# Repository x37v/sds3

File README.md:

sds3
====

SDS3 clone project - these files have not been succesfully built yet

Long thread on electro-music.com that led to fixes in the original schematic from boardmember Theff, and a working SMT run from xpmtl
http://electro-music.com/forum/topic-16985.html&postorder=asc

some troubleshooting info here: http://electro-music.com/forum/topic-16985-300.html

xpmtl's SMT design is here:
http://xpmtl.net/sdiy/projects/simmons-sds-3-voice/

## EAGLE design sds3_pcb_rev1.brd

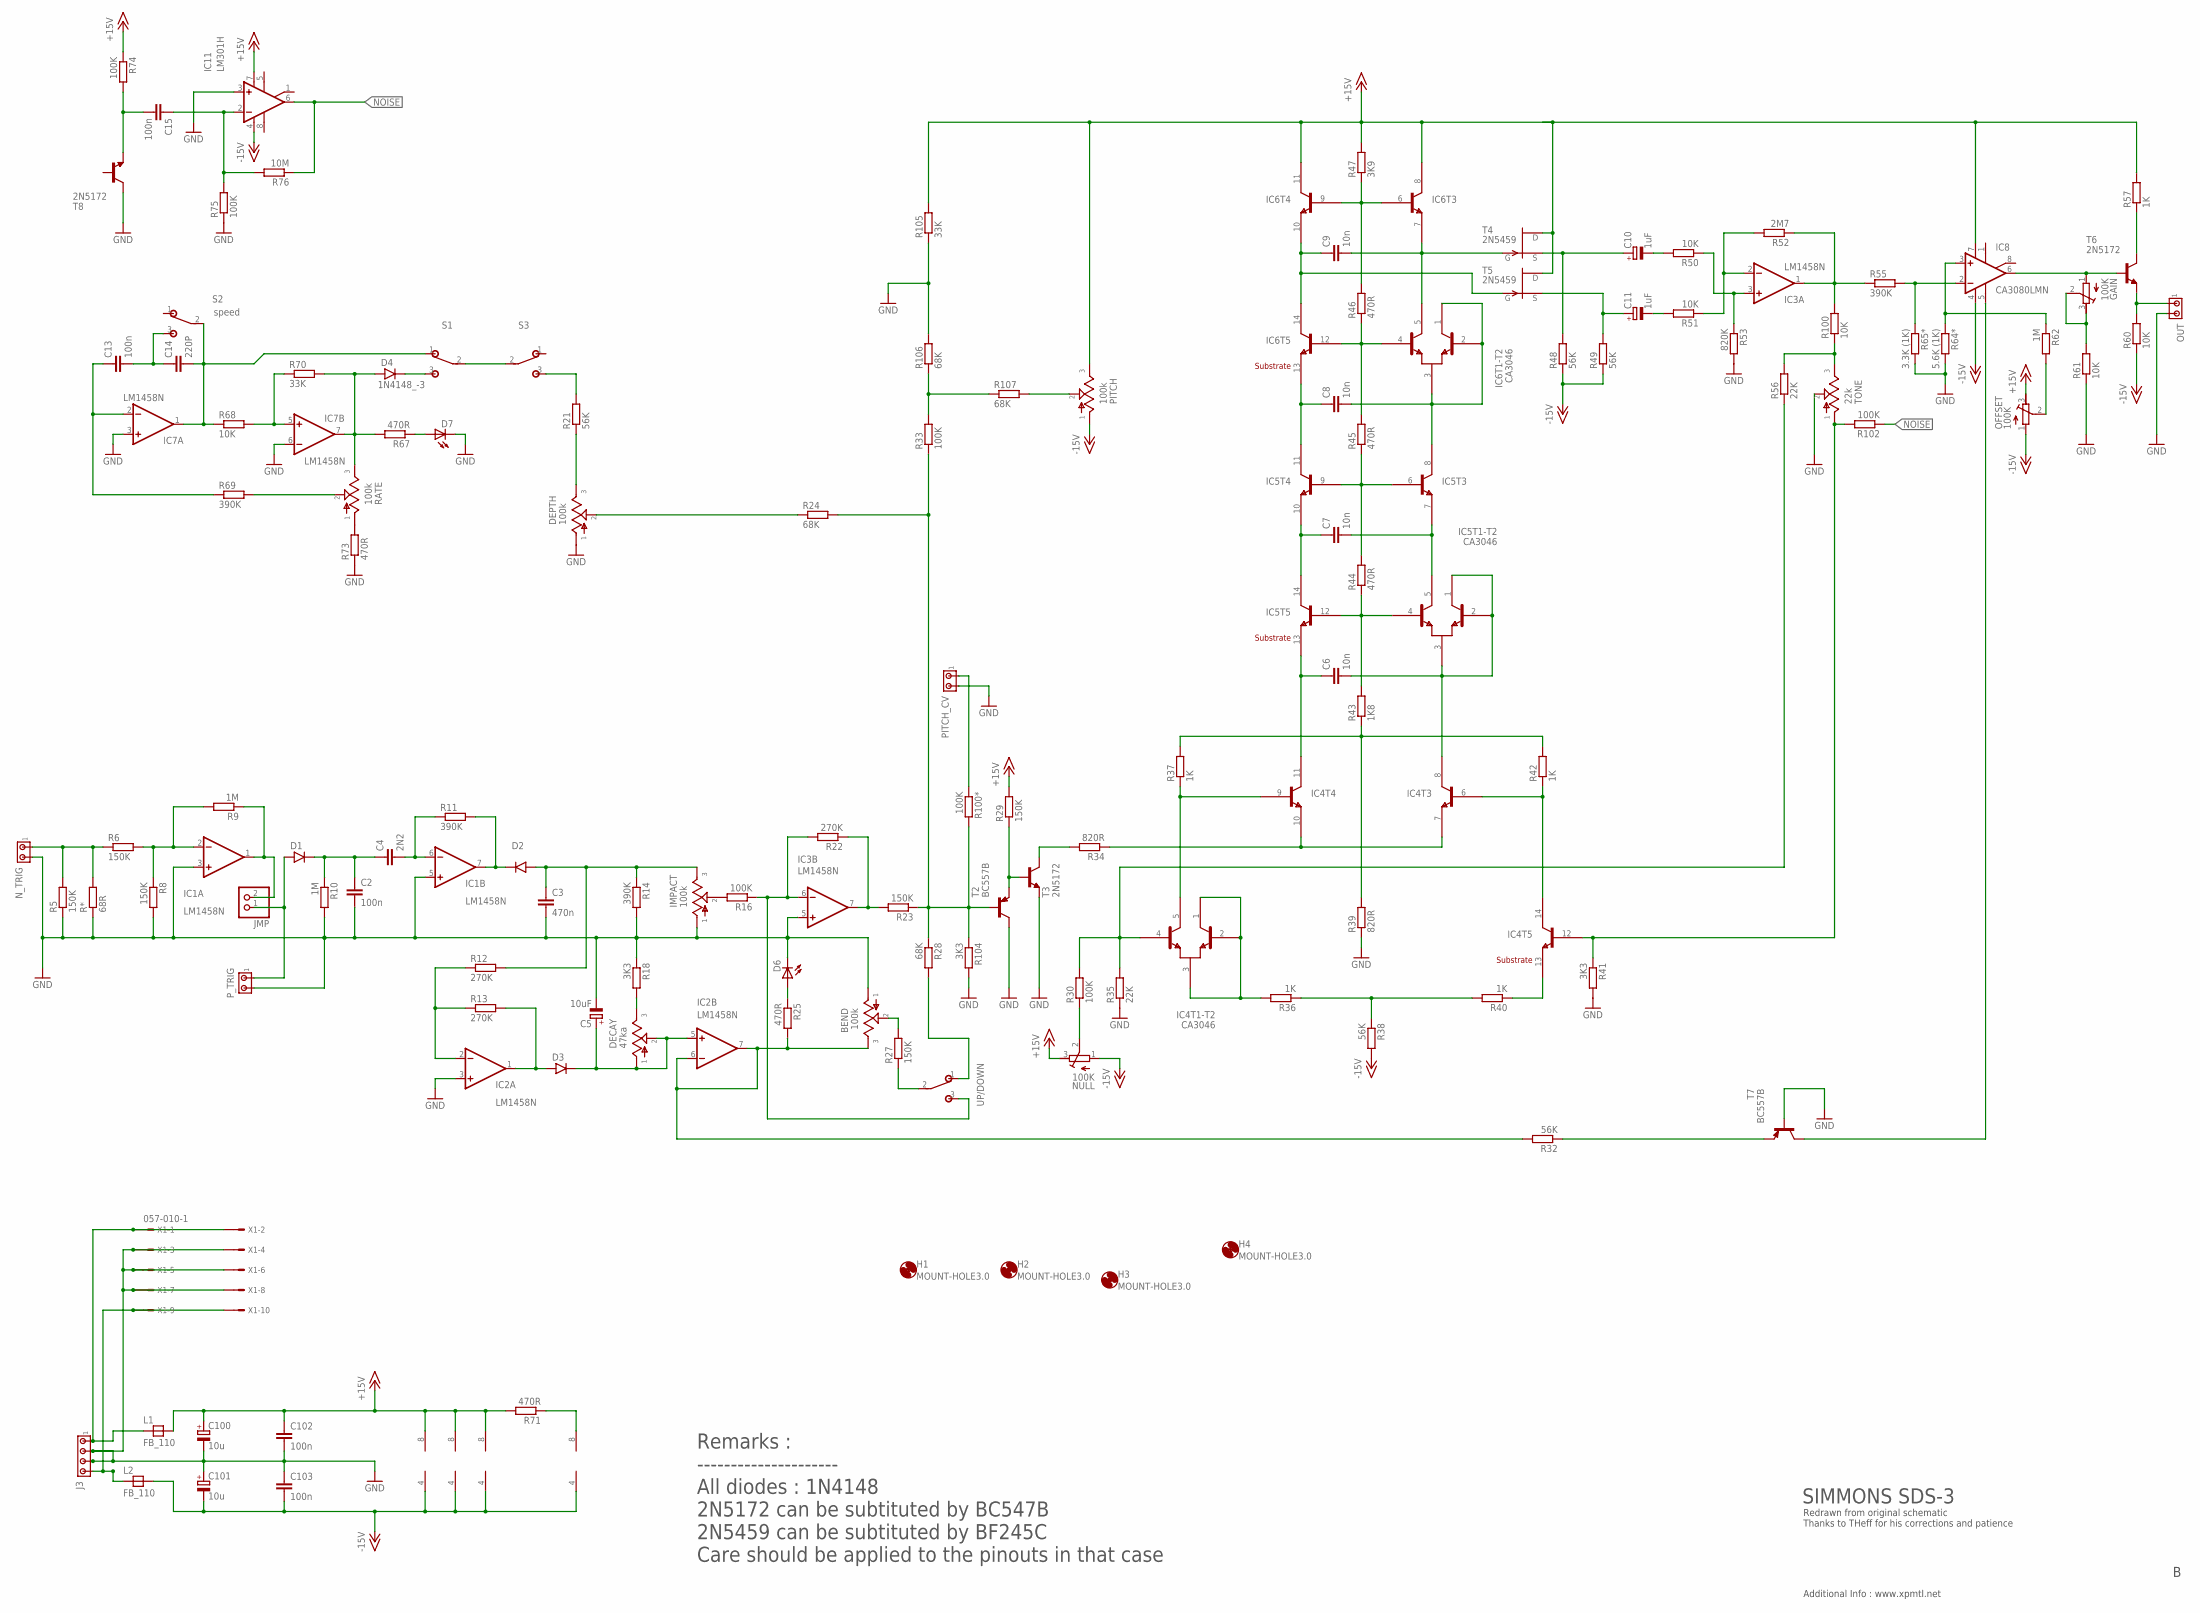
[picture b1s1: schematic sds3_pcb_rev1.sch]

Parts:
BEND: 100k; POT
C2, C13, C15, C102, C103: 100n; C050-025X075
C3: 470n; C050-025X075
C4: 2N2; C050-025X075
C5: 10uF; E2,5-6
C6, C7, C8, C9: 10n; C050-025X075
C10, C11: 1uF; E2,5-6
C14: 220P; C050-025X075
C100, C101: 10u; B45181A
D1, D2, D3, D4: 1N4148_-3; DO35-3
D6, D7: LED5MM
DECAY: 47ka; POT
DEPTH: 100k; POT
GAIN: 100K; RTRIM3296W
H1, H2, H3, H4: MOUNT-HOLE3.0; 3,0
IC1, IC2, IC3, IC7: LM1458N; DIL08
IC4, IC5, IC6: CA3046; DIL14
IC8: CA3080LMN; DIL08
IC11: LM301H; DIL08
IMPACT: 100k; POT
J3: MTA04-156; 1X4MTA
JMP: PINHD-1X2; 1X02
L1, L2: FB_110; FB-110
NULL: 100K; RTRIM3296W
N_TRIG: MTA02-100; 10X02MTA
OFFSET: 100K; RTRIM3296W
OUT: MTA02-100; 10X02MTA
PITCH: 100k; POT
PITCH_CV: MTA02-100; 10X02MTA
P_TRIG: MTA02-100; 10X02MTA
R5, R6, R8, R23, R27, R29: 150K; 0309V
R9, R10, R62: 1M; 0309V
R11, R14, R55, R69: 390K; 0309V
R12, R13, R22: 270K; 0309V
R16, R30, R33, R74, R75, R100*, R102: 100K; 0309V
R18, R41, R104: 3K3; 0309V
R21, R32, R38, R48, R49: 56K; 0309V
R24, R28, R106, R107: 68K; 0309V
R25, R44, R45, R46, R67, R71, R73: 470R; 0309V
R34, R39: 820R; 0309V
R35, R56: 22K; 0309V
R36, R37, R40, R42, R57: 1K; 0309V
R43: 1K8; 0309V
R47: 3K9; 0309V
R50, R51, R60, R61, R68, R100: 10K; 0309V
R52: 2M7; 0309V
R53: 820K; 0309V
R64*: 5.6K (1K); 0309V
R65*: 3.3K (1K); 0309V
R70, R105: 33K; 0309V
R76: 10M; 0309V
R*: 68R; 0309V
RATE: 100k; POT
S1: shape; SPDT
S2: speed; SPDT
S3: on/off; SPDT
T2, T7: BC557B; TO92-EBC
T3, T6, T8: 2N5172; TO92-LINE
T4, T5: 2N5459; TO92-FET2
TONE: 22k; POT
UP/DOWN: SPDTPADS; SPDT
X1: 057-010-1

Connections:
+15V: C100.+, C102.1, IC1.8 (V+), IC2.8 (V+), IC3.8 (V+), IC6.8 (C), IC6.11 (C), IC8.7 (V+), IC11.7 (V+), L1.2, NULL.3 (E), OFFSET.3 (E), PITCH.3, R29.2, R47.2, R57.2, R71.2, R74.1, R105.2, T4.D, T5.D
-15V: C101.-, C103.2, IC1.4 (V-), IC2.4 (V-), IC3.4 (V-), IC7.4 (V-), IC8.4 (V-), IC11.4 (V-), L2.2, NULL.1 (A), OFFSET.1 (A), PITCH.1, R38.2, R48.1, R49.1, R60.1
GND: BEND.1, C2.2, C3.2, C5.-, C100.-, C101.+, C102.2, C103.1, D6.K (C), D7.K (C), DEPTH.1, IC1.3 (+IN), IC1.5 (+IN), IC2.3 (+IN), IC3.5 (+IN), IC7.3 (+IN), IC7.6 (-IN), IC11.3 (+IN), IMPACT.1, J3.2, J3.3, N_TRIG.2, OUT.2, PITCH_CV.2, P_TRIG.2, R5.1, R8.2, R10.2, R14.2, R18.1, R35.1, R39.1, R41.2, R53.2, R61.1, R64*.2, R65*.2, R73.1, R75.1, R104.2, R105.1, R106.2, R*.1, T2.C, T3.E, T7.B, T8.C, TONE.2, X1.3, X1.4, X1.5, X1.6, X1.7, X1.8
unnamed: C9.1, IC6.10 (E), IC6.14 (C), T5.G
unnamed: IC6.4 (B2), IC6.12 (B), R45.2, R46.1
unnamed: C9.2, IC6.5 (C2), IC6.7 (E), T4.G
unnamed: IC6.6 (B), IC6.9 (B), R46.2, R47.1
unnamed: C11.-, R51.2
unnamed: C8.1, IC5.11 (C), IC6.13 (E)
unnamed: C8.2, IC5.8 (C), IC6.1 (C1), IC6.2 (B1), IC6.3 (E)
unnamed: IC5.6 (B), IC5.9 (B), R44.2, R45.1
unnamed: C7.1, IC5.10 (E), IC5.14 (C)
unnamed: C7.2, IC5.5 (C2), IC5.7 (E)
unnamed: IC5.4 (B2), IC5.12 (B), R43.2, R44.1
unnamed: C6.1, IC4.11 (C), IC5.13 (E)
unnamed: C6.2, IC4.8 (C), IC5.1 (C1), IC5.2 (B1), IC5.3 (E)
unnamed: IC4.6 (B), IC4.14 (C), R42.1
unnamed: IC4.5 (C2), IC4.9 (B), R37.1
unnamed: R37.2, R39.2, R42.2, R43.1
unnamed: IC4.7 (E), IC4.10 (E), R34.1
unnamed: IC4.1 (C1), IC4.2 (B1), IC4.3 (E), R36.2
unnamed: R36.1, R38.1, R40.2
unnamed: IC4.13 (E), R40.1
unnamed: IC4.4 (B2), R30.2, R35.2, R56.1
unnamed: C10.-, R50.2
unnamed: C10.+, R48.2, T4.S
unnamed: C11.+, R49.2, T5.S
unnamed: IC3.3 (+IN), R50.1, R53.1
unnamed: IC3.2 (-IN), R51.1, R52.2
unnamed: IC3.1 (OUT), R52.1, R55.1, R100.2
unnamed: IC8.2 (-IN), R55.2, R65*.1
unnamed: IC8.3 (+IN), R62.1, R64*.1
unnamed: GAIN.1 (A), IC8.6 (OUT), T6.B
unnamed: R57.1, T6.C
unnamed: OUT.1, R60.2, T6.E
unnamed: R32.1, T7.E
unnamed: IC8.5 (OPT), T7.C
unnamed: R56.2, R100.1, TONE.3
unnamed: IC4.12 (B), R41.1, R102.2, TONE.1
unnamed: OFFSET.2 (S), R62.2
unnamed: NULL.2 (S), R30.1
unnamed: R23.1, R24.2, R28.1, R33.1, R100*.2, R104.1, T2.B
unnamed: R29.1, T2.E, T3.B
unnamed: R34.2, T3.C
unnamed: IC3.7 (OUT), R22.1, R23.2
unnamed: IC3.6 (-IN), R16.1, R22.2, UP/DOWN.3 (S)
unnamed: IC1.1 (OUT), JMP.2, R9.1
unnamed: IMPACT.2, R16.2
unnamed: C3.1, D2.A, IMPACT.3, R12.2, R14.1
unnamed: D2.C, IC1.7 (OUT), R11.2
unnamed: C4.2, IC1.6 (-IN), R11.1
unnamed: C2.1, C4.1, D1.C, R10.1
unnamed: IC2.2 (-IN), R12.1, R13.1
unnamed: IC1.2 (-IN), R6.2, R8.1, R9.2
unnamed: N_TRIG.1, R5.2, R6.1, R*.2
unnamed: D3.A, IC2.1 (OUT), R13.2
unnamed: BEND.3, IC2.6 (-IN), IC2.7 (OUT), R25.2, R32.2
unnamed: C5.+, D3.C, DECAY.1, DECAY.2, IC2.5 (+IN)
unnamed: DECAY.3, R18.2
unnamed: D6.A, R25.1
unnamed: R27.1, UP/DOWN.2
unnamed: BEND.2, R27.2
unnamed: R28.2, UP/DOWN.1 (O)
unnamed: R21.2, S3.3 (S)
unnamed: C15.2, R74.2, T8.E
unnamed: C15.1, IC11.2 (-IN), R75.2, R76.2
unnamed: PITCH_CV.1, R100*.1
unnamed: R73.2, RATE.1
unnamed: GAIN.2 (S), GAIN.3 (E), R61.2
unnamed: C14.2, IC7.1 (OUT), R68.1, S1.1 (O), S2.2
unnamed: IC7.5 (+IN), R68.2, R70.1
unnamed: D4.A, IC7.7 (OUT), R67.2, R70.2, RATE.3
unnamed: R69.2, RATE.2
unnamed: C13.1, IC7.2 (-IN), R69.1
unnamed: C13.2, C14.1, S2.3 (S)
unnamed: D4.C, S1.3 (S)
unnamed: S1.2, S3.2
unnamed: DEPTH.3, R21.1
unnamed: DEPTH.2, R24.1
unnamed: PITCH.2, R107.2
unnamed: R33.2, R106.1, R107.1
unnamed: D7.A, R67.1
unnamed: J3.1, L1.1, X1.1, X1.2
unnamed: J3.4, L2.1, X1.9, X1.10
unnamed: IC7.8 (V+), R71.1
unnamed: D1.A, JMP.1, P_TRIG.1
NOISE: IC11.6 (OUT), R76.1, R102.1

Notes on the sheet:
SIMMONS SDS-3
Redrawn from original schematic Thanks to THeff for his corrections and patience
Remarks : --------------------- All diodes : 1N4148 2N5172 can be subtituted by BC547B 2N5459 can be subtituted by BF245C Care should be applied to the pinouts in that case
Additional Info : www.xpmtl.net

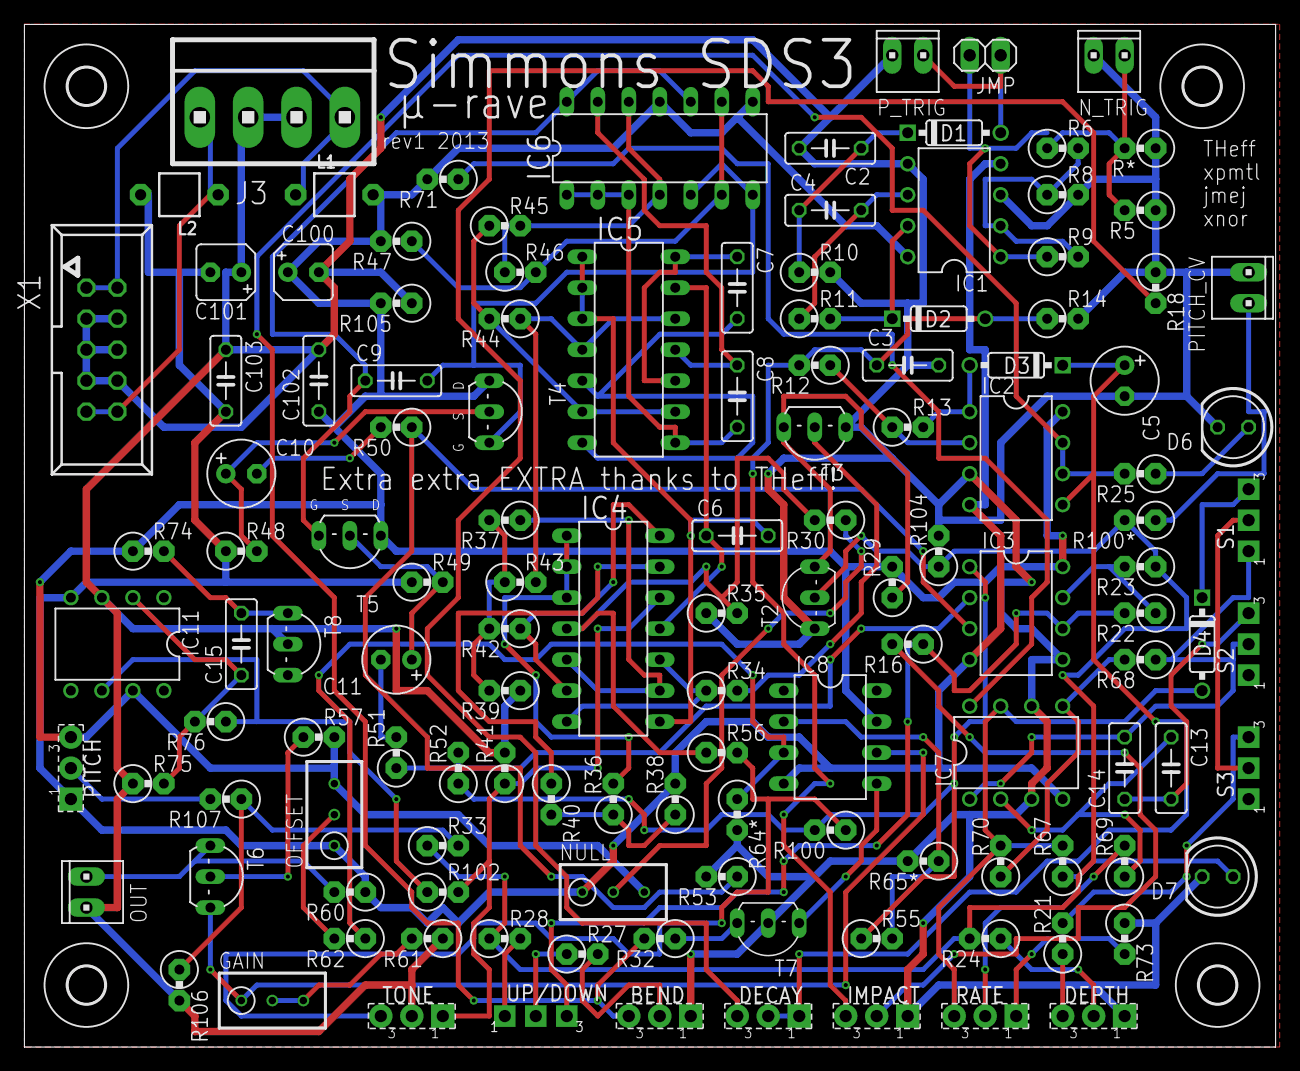
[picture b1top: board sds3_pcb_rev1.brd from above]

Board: 2 copper layers, 102.5 x 83.8 mm, 133 parts (0 on the bottom side), 87 nets.

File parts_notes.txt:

a 2 of 1uF: 	C10, C11
2 of 10u: 	C100, C101
a 1 of 220P: 	C14
a 5 of 100n: 	C2, C13, C15, C102, C103
1 of 470n: 	C3
a 1 of 2N2: 	C4
a 1 of 10uF: 	C5
a 4 of 10n: 	C6, C7, C8, C9
4 of 1N4148_-3: 	D1, D2, D3, D4

3 of 100K: 	[TRIM] GAIN, NULL, OFFSET, 
1 of 47ka: 	DECAY
5 of 100K BEND, DEPTH, IMPACT, PITCH, RATE
1 of 22k: 	TONE

a 4 of LM1458N: 	IC1, IC2, IC3, IC7
a 1 of LM301H: 	IC11
3 of CA3046: 	IC4, IC5, IC6
1 of CA3080LMN: 	IC8

*2 of FB_110: 	L1, L2

ORIGINALLY
	R64: 5.6K
	R65: 3.3K

7 of 100K: R16, R30, R33, R74, R75, R100*, R102
1 of 68R: 	R*
*4 of 390K: 	R11, R14, R55, R69
*3 of 270K: 	R12, R13, R22
*3 of 3K3: 	R18, R41, R104
*5 of 56K: 	R21, R32, R38, R48, R49
4 of 68K: 	R24, R28, R106, R107
7 of 470R: 	R25, R44, R45, R46, R67, R71, R73
*2 of 820R: 	R34, R39
*2 of 22K: 	R35, R56
*7 of 1K: 	R36, R37, R40, R42, R57, R64, R65
*1 of 1K8: 	R43
1 of 3K9: 	R47 [jesse stuffed]
*6 of 150K: 	R5, R6, R8, R23, R27, R29
*6 of 10K: 	R50, R51, R60, R61, R68, R100
*1 of 2M7: 	R52
*1 of 820K: 	R53
*2 of 33K: 	R70, R105
*1 of 10M: 	R76
*3 of 1M: 	R9, R10, R62

1 of shape: 	S1
1 of speed: 	S2
1 of on/off: 	S3
a 2 of BC557B: 	T2, T7
a 3 of 2N5172: 	T3, T6, T8
a 2 of 2N5459: 	T4, T5  [pull off old board]
1 of 057-010-1: 	X1

trimmer holes are too small and only support pins on a line
pads on some of the 8 pin ics are small
r32, r27 labels ambigious
r43 label illegible

need:
68R
68k
470R
3.9K
8 pin sockets
better trimmers: 72-T93YA-100K 
470nF cap [0.47u]

c2, t2 label could be better
c100 and c101 have weird package on board [and should be labeled uF]
Original values for R64 and 65 [add stars?]
R100* is starred because it is fixed at 100K but was part of the run generator before
Actually, there is an R100 and R100*
D7 via is SO close!
S3 and S2 should only have 2 pads
trimmers should be 1 turn..

Alex stuffed 47KA pot with 50K linear

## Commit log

2013-08-07 initial project for sds3
